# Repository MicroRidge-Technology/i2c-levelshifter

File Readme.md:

# I2c Level Shifter

Quick and dirty level shifter for i2c.

Meant to be used with *HiLetgo CP2112 Debug board*
https://a.co/d/1jTiATS

[Schematic](doc/i2c_levelshifter.pdf)

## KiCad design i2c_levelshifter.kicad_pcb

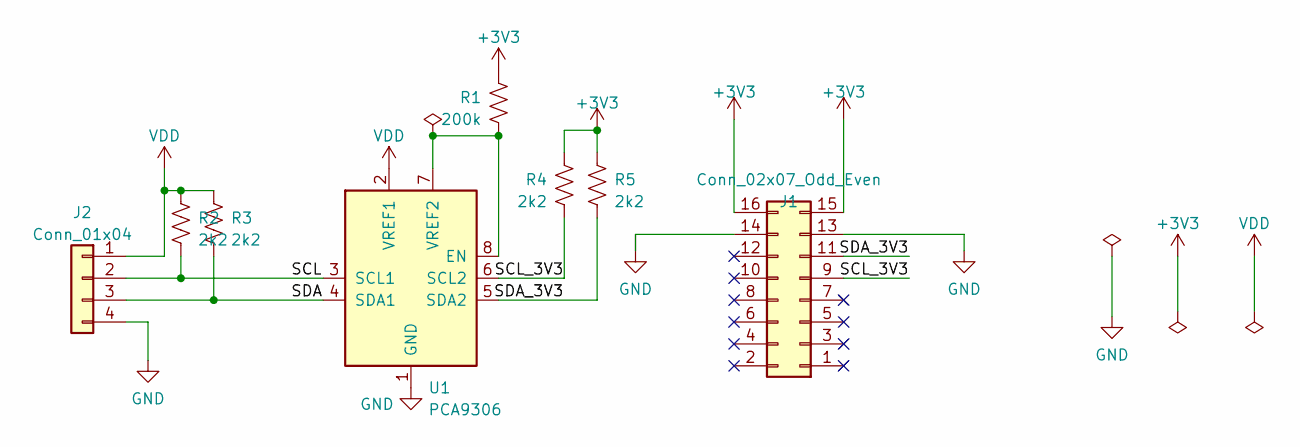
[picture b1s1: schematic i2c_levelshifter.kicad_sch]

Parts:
J1: Conn_02x07_Odd_Even; PinSocket_2x08_P2.54mm_Vertical; LCSC Part # C72555
J2: Conn_01x04; PinHeader_1x04_P2.54mm_Vertical
R1: 200k; R_0603_1608Metric; LCSC Part # C25811
R2, R3, R4, R5: 2k2; R_0603_1608Metric; LCSC Part # C4190
U1: PCA9306; VSSOP-8_2.3x2mm_P0.5mm; LCSC Part # C129510

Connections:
+3V3: J1.15, J1.16, R1.1, R4.1, R5.1
/SCL: J2.2, R2.2, U1.3 (SCL1)
/SCL_3V3: J1.9, R4.2, U1.6 (SCL2)
/SDA: J2.3, R3.2, U1.4 (SDA1)
/SDA_3V3: J1.11, R5.2, U1.5 (SDA2)
GND: J1.13, J1.14, J2.4, U1.1 (GND)
unnamed: R1.2, U1.7 (VREF2), U1.8 (EN)
VDD: J2.1, R2.1, R3.1, U1.2 (VREF1)

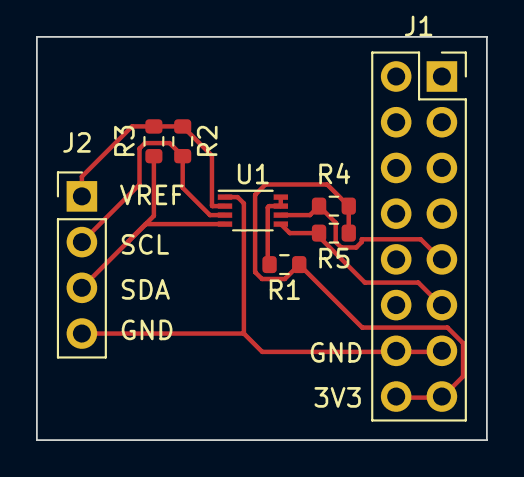
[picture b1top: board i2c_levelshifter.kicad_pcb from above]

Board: 2 copper layers, 25.0 x 22.4 mm, 8 parts (0 on the bottom side), 8 nets.

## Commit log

2024-06-19 Add a tiny bit of doc
2024-06-19 add note about i2c usb adapter
